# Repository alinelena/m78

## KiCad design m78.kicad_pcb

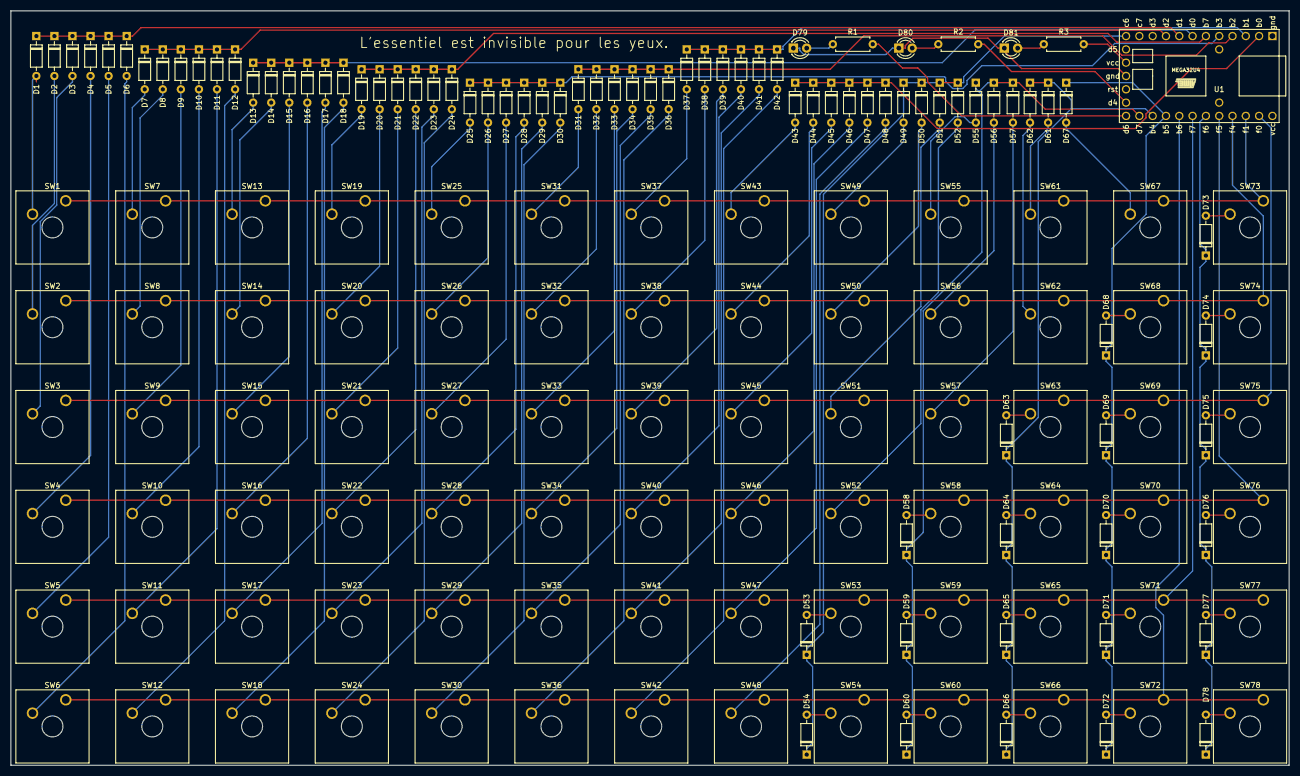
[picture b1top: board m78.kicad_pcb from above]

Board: 2 copper layers, 244.0 x 144.0 mm, 163 parts (0 on the bottom side), 104 nets.

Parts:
D1, D2, D3, D4, D5, D6, D7, D8, D9, D10, D11, D12, D13, D14, D15, D16, D17, D18, D19, D20, D21, D22, D23, D24, D25, D26, D27, D28, D29, D30, D31, D32, D33, D34, D35, D36, D37, D38, D39, D40, D41, D42, D43, D44, D45, D46, D47, D48, D49, D50, D51, D52, D53, D54, D55, D56, D57, D58, D59, D60, D61, D62, D63, D64, D65, D66, D67, D68, D69, D70, D71, D72, D73, D74, D75, D76, D77: D; diode_v
D78: D; diode_h
D79, D80, D81: LED; LED_D3.0mm_Clear
R1, R2, R3: R; R_Axial_DIN0207_L6.3mm_D2.5mm_P7.62mm_Horizontal
SW1, SW2, SW3, SW4, SW5, SW6, SW7, SW8, SW9, SW10, SW11, SW12, SW13, SW14, SW15, SW16, SW17, SW18, SW19, SW20, SW21, SW22, SW23, SW24, SW25, SW26, SW27, SW28, SW29, SW30, SW31, SW32, SW33, SW34, SW35, SW36, SW37, SW38, SW39, SW40, SW41, SW42, SW43, SW44, SW45, SW46, SW47, SW48, SW49, SW50, SW51, SW52, SW53, SW54, SW55, SW56, SW57, SW58, SW59, SW60, SW61, SW62, SW63, SW64, SW65, SW66, SW67, SW68, SW69, SW70, SW71, SW72, SW73, SW74, SW75, SW76, SW77, SW78: mx; SW_Cherry_MX_1.00u_Plate
U1: TEENSY2.0; Teensy2.0-pins

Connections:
unnamed: D1.2, SW1.2
unnamed: D2.2, SW2.2
unnamed: D3.2, SW3.2
unnamed: D4.2, SW4.2
unnamed: D5.2, SW5.2
unnamed: D6.2, SW6.2
unnamed: D7.2, SW7.2
unnamed: D8.2, SW8.2
unnamed: D9.2, SW9.2
unnamed: D10.2, SW10.2
unnamed: D11.2, SW11.2
unnamed: D12.2, SW12.2
unnamed: D13.2, SW13.2
unnamed: D14.2, SW14.2
unnamed: D15.2, SW15.2
unnamed: D16.2, SW16.2
unnamed: D17.2, SW17.2
unnamed: D18.2, SW18.2
unnamed: D19.2, SW19.2
unnamed: D20.2, SW20.2
unnamed: D21.2, SW21.2
unnamed: D22.2, SW22.2
unnamed: D23.2, SW23.2
unnamed: D24.2, SW24.2
unnamed: D25.2, SW25.2
unnamed: D26.2, SW26.2
unnamed: D27.2, SW27.2
unnamed: D28.2, SW28.2
unnamed: D29.2, SW29.2
unnamed: D30.2, SW30.2
unnamed: D31.2, SW31.2
unnamed: D32.2, SW32.2
unnamed: D33.2, SW33.2
unnamed: D34.2, SW34.2
unnamed: D35.2, SW35.2
unnamed: D36.2, SW36.2
unnamed: D37.2, SW37.2
unnamed: D38.2, SW38.2
unnamed: D39.2, SW39.2
unnamed: D40.2, SW40.2
unnamed: D41.2, SW41.2
unnamed: D42.2, SW42.2
unnamed: D43.2, SW43.2
unnamed: D44.2, SW44.2
unnamed: D45.2, SW45.2
unnamed: D46.2, SW46.2
unnamed: D47.2, SW47.2
unnamed: D48.2, SW48.2
unnamed: D49.2, SW49.2
unnamed: D50.2, SW50.2
unnamed: D51.2, SW51.2
unnamed: D52.2, SW52.2
unnamed: D53.2, SW53.2
unnamed: D54.2, SW54.2
unnamed: D55.2, SW55.2
unnamed: D56.2, SW56.2
unnamed: D57.2, SW57.2
unnamed: D58.2, SW58.2
unnamed: D59.2, SW59.2
unnamed: D60.2, SW60.2
unnamed: D61.2, SW61.2
unnamed: D62.2, SW62.2
unnamed: D63.2, SW63.2
unnamed: D64.2, SW64.2
unnamed: D65.2, SW65.2
unnamed: D66.2, SW66.2
unnamed: D67.2, SW67.2
unnamed: D68.2, SW68.2
unnamed: D69.2, SW69.2
unnamed: D70.2, SW70.2
unnamed: D71.2, SW71.2
unnamed: D72.2, SW72.2
unnamed: D73.2, SW73.2
unnamed: D74.2, SW74.2
unnamed: D75.2, SW75.2
unnamed: D76.2, SW76.2
unnamed: D77.2, SW77.2
unnamed: D78.2, SW78.2
unnamed: D79.2, R1.1
unnamed: D80.2, R2.1
unnamed: D81.2, R3.1
c0: D1.1, D2.1, D3.1, D4.1, D5.1, D6.1, U1.8
c1: D7.1, D8.1, D9.1, D10.1, D11.1, D12.1, U1.9
c2: D13.1, D14.1, D15.1, D16.1, D17.1, D18.1, U1.7
c3: D19.1, D20.1, D21.1, D22.1, D23.1, D24.1, U1.6
c4: D25.1, D26.1, D27.1, D28.1, D29.1, D30.1, U1.5
c5: D31.1, D32.1, D33.1, D34.1, D35.1, D36.1, U1.4
c6: D37.1, D38.1, D39.1, D40.1, D41.1, D42.1, U1.3
c7: D43.1, D44.1, D45.1, D46.1, D47.1, D48.1, U1.2
c8: D49.1, D50.1, D51.1, D52.1, D53.1, D54.1, U1.12
c9: D55.1, D56.1, D57.1, D58.1, D59.1, D60.1, U1.19
c10: D61.1, D62.1, D63.1, D64.1, D65.1, D66.1, U1.20
c11: D67.1, D68.1, D69.1, D70.1, D71.1, D72.1, U1.21
c12: D73.1, D74.1, D75.1, D76.1, D77.1, D78.1, U1.24
cpp: R1.2, U1.18
f90: R2.2, U1.17
gnd: D79.1, D80.1, D81.1, U1.15
pwr: R3.2, U1.14
r0: SW1.1, SW7.1, SW13.1, SW19.1, SW25.1, SW31.1, SW37.1, SW43.1, SW49.1, SW55.1, SW61.1, SW67.1, SW73.1, U1.27
r1: SW2.1, SW8.1, SW14.1, SW20.1, SW26.1, SW32.1, SW38.1, SW44.1, SW50.1, SW56.1, SW62.1, SW68.1, SW74.1, U1.26
r2: SW3.1, SW9.1, SW15.1, SW21.1, SW27.1, SW33.1, SW39.1, SW45.1, SW51.1, SW57.1, SW63.1, SW69.1, SW75.1, U1.28
r3: SW4.1, SW10.1, SW16.1, SW22.1, SW28.1, SW34.1, SW40.1, SW46.1, SW52.1, SW58.1, SW64.1, SW70.1, SW76.1, U1.25
r4: SW5.1, SW11.1, SW17.1, SW23.1, SW29.1, SW35.1, SW41.1, SW47.1, SW53.1, SW59.1, SW65.1, SW71.1, SW77.1, U1.23
r5: SW6.1, SW12.1, SW18.1, SW24.1, SW30.1, SW36.1, SW42.1, SW48.1, SW54.1, SW60.1, SW66.1, SW72.1, SW78.1, U1.22

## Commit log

2020-11-20 initial pain
2020-11-20 rename to something more sensible
2020-11-20 schema
2020-11-20 pcb pic
2020-11-21 diodes in rows
2020-11-21 Revert "diodes in rows"
    This reverts commit 9845cd0533da21a297a661dd2d085098a01597ee.
2020-11-22 diodes in columns
